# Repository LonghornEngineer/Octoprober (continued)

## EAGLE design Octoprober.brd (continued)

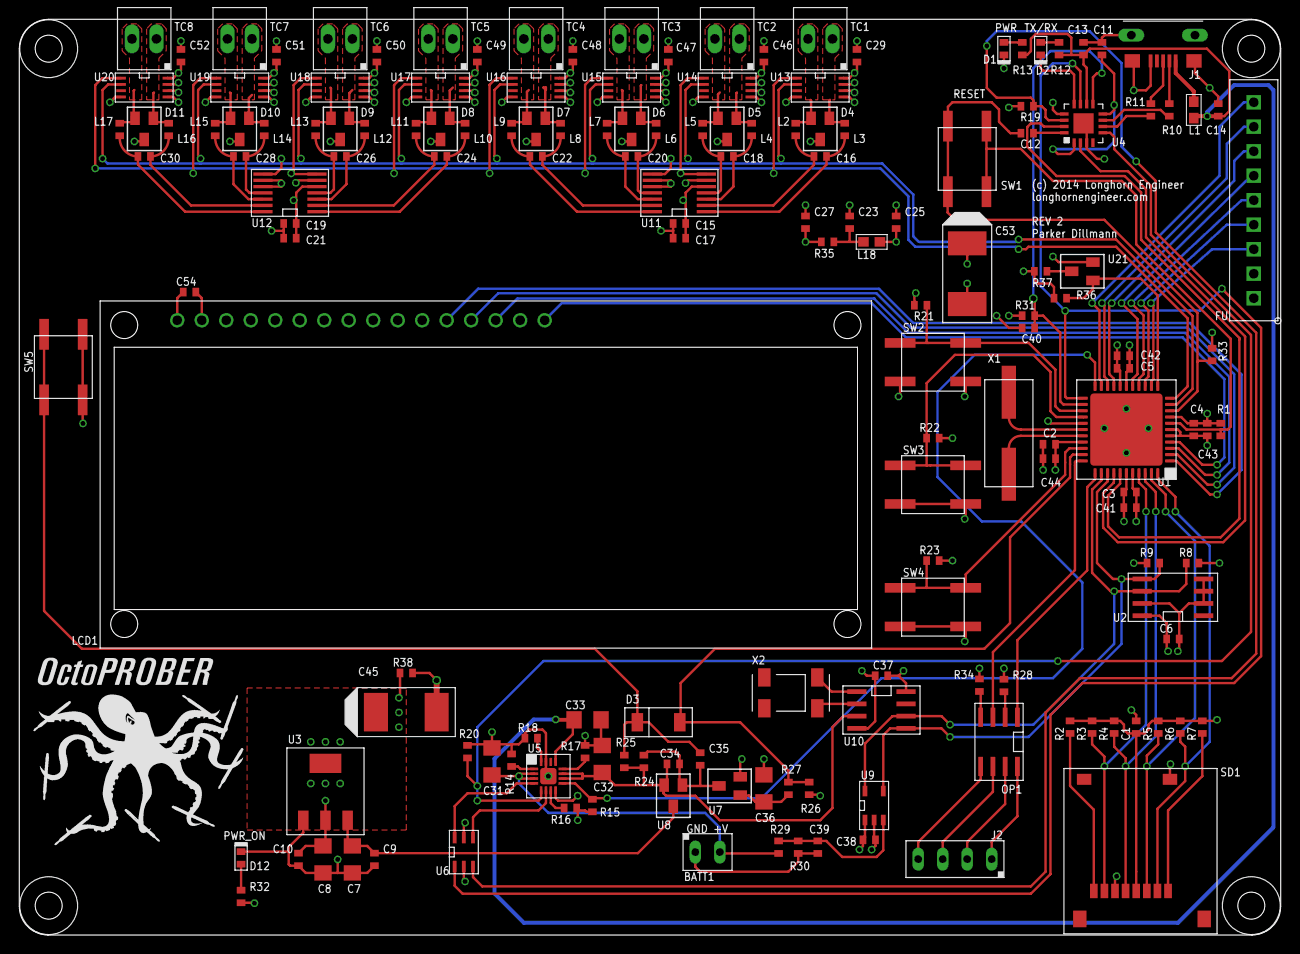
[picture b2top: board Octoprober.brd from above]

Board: 4 copper layers, 130.8 x 95.0 mm, 171 parts (0 on the bottom side), 109 nets.

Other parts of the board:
U$3, U$4, U$5, U$6: MOUNT_HOLE_2.8MM

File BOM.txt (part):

Partlist exported from C:/Users/ParkerD/Documents/GitHub/Octoprober/Octoprober.sch at 2/24/2014 9:25:52 PM

Qty Value                 Device                        Package                       Parts                                                                                                                     Description                    
1                         HD44780_LCD1602_COUNTERSINK   CHAR_DISPLAY_1602_COUNTERSINK LCD1                                                                                                                                                     
1                         PH_1X04HEADER_PTH             HEADER_01X04_PTH              J2                                                                                                                        4 Pin Connectors               
8   0.01uF                CAPACITOR_NON_POLAR0402       0402                          C16, C18, C20, C22, C24, C26, C28, C30                                                                                    Capacitor Non Polarized        
26  0.1uF                 CAPACITOR_NON_POLAR0402       0402                          C1, C2, C3, C4, C5, C6, C9, C10, C11, C12, C13, C14, C15, C17, C19, C21, C23, C25, C27, C29, C34, C35, C37, C38, C39, C40 Capacitor Non Polarized        
1   1.13K                 RESISTOR0402                  0402                          R18                                                                                                                       Resistors                      
1   1.18K                 RESISTOR0402                  0402                          R17                                                                                                                       Resistors                      
3   100K                  RESISTOR0402                  0402                          R24, R26, R29                                                                                                             Resistors                      
1   10118193-0001LF       USB10118193-0001LF            10118193-0001LF               J1                                                                                                                                                       
20  10K                   RESISTOR0402                  0402                          R1, R2, R3, R4, R5, R6, R7, R8, R9, R14, R15, R16, R19, R20, R21, R22, R23, R25, R31, R33                                 Resistors                      
6   10uF                  CAPACITOR_NON_POLAR1206       1206                          C7, C8, C31, C32, C33, C36                                                                                                Capacitor Non Polarized        
2   120                   RESISTOR0402                  0402                          R28, R34                                                                                                                  Resistors                      
2   22                    RESISTOR0402                  0402                          R10, R11                                                                                                                  Resistors                      
1   254K                  RESISTOR0402                  0402                          R30                                                                                                                       Resistors                      
8   282834-2              PH_1X02SCREW_TERM             HEADER_01X02_PTH_SCREWTERM    TC1, TC2, TC3, TC4, TC5, TC6, TC7, TC8                                                                                    2 pin connectors               
1   300K                  RESISTOR0402                  0402                          R27                                                                                                                       Resistors                      
3   330                   RESISTOR0402                  0402                          R12, R13, R32                                                                                                             Resistors                      
1   502570-0893           SD_CARD502570-0893            502570-0893                   SD1                                                                                                                                                      
3   598-8070-107F         LED_SINGLE0402                LED_0402                      D1, D2, D12                                                                                                                                              
1   74HC2G04GV,125        74HCT2G04GV,125TTSOP-6        TTSOP-6                       U6                                                                                                                                                       
1   ABLS3-6.000MHZ-D4Y-T  CRYSTALHC-49                  HC-49/US_SM                   X1                                                                                                                                                       
1   ABS25-32.768KHz-1-T   CRYSTAL8MM_X_3.8MM            8MM_X_3.8MM                   X2                                                                                                                                                       
1   ACPL-227              ACPL-227SOIC-8                SOIC-8                        OP1                                                                                                                                                      
1   ADP3338AKCZ-3.3-RL    FIXED_VOLTAGE_REGSOT-223_ALT  SOT-223                       U3                                                                                                                                                       
16  BK1005HM471-T         INDUCTOR0402                  0402                          L2, L3, L4, L5, L6, L7, L8, L9, L10, L11, L12, L13, L14, L15, L16, L17                                                    Inductors                      
1   BQ24075RGTT           BQ2407XQFN-16                 QFN-16_BOT_PAD                U5                                                                                                                                                       
1   CAT24C512WI-GT3       CAT24M01XI-T2SOIC-8_W         SOIC-8_W                      U2                                                                                                                                                       
1   DS1340Z-33+           DS1340SOIC-8                  SOIC-8                        U18                                                                                                                                                      
5   EVQ-Q2203W            SPSTEVQ-Q2203W                EVQ-Q2203W                    SW1, SW2, SW3, SW4, SW5                                                                                                   SPST Switches                  
1   FT230XQ-R             FT230XQFN-16                  QFN-16                        U4                                                                                                                        Manufacturer Part #: FT230XS-R 
1   LHE_FRAME             LHE_FRAME                     LHE_FRAME                     U$1                                                                                                                                                      
8   MAX31855KASA+         MAX31855SO-8                  SO-8                          U7, U8, U9, U10, U11, U12, U13, U14                                                                                                                      
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
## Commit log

2013-12-16 Commit first schematic. Need to figure out power.
2013-12-16 Added lithium battery. Still need to add charger.
2013-12-17 Added BQ24075RGTT for charging.
2013-12-18 Still need Battery Monitoring Solution
2013-12-18 Uploading PDF of Logo
2013-12-19 Added Soft power switch
    Soft power circuit to enable MCU to initiate a shutdown of the system to
    prevent corruption of the SD Card.
2013-12-19 Added ADC. Might use it for battery voltage level.
2013-12-31 Created Board. Still need to figure out connector
2014-01-06 Worked on the layout some more.
    Still need lots of work and connectors.
2014-01-07 Add optocouple.
2014-01-07 Finished preliminary routing
2014-01-07 Added Schematic image.
2014-01-10 Added RTC.
2014-01-10 New Schematic image
2014-01-10 Rerouted I/O for LCD around mounting hole
2014-01-11 Working on Silkscreen
2014-01-12 Fixed some traces. Looking good. Silkscreen next.
2014-01-13 Added TVS to TC lines.
2014-01-13 Finished REV0.
2014-01-14 Added ADC MCP3021 to monitor battery
2014-01-14 Cam files REV0
2014-01-27 Push Schematic image
2014-01-27 removed camfiles
2014-01-27 removed old layout images.
2014-01-28 Added part values and created BOM.txt
2014-01-28 Fixed some part numbers
2014-01-28 Finished BOM...I hope.
2014-01-31 Swapped VCC and VDD on display
2014-01-31 Updated display footprint
2014-01-31 Evened out power traces on C17
2014-02-04 Changed footprint for Regulator
2014-02-04 Changed FT230X RST to be controlled by PROP
2014-02-04 Added cap to FT230X RST line.
2014-02-04 Fixed screw terminal footprints.
2014-02-05 Added Code section for OctoPROBER
2014-02-05 Added README.md to code
2014-02-05 Cleaned up LCD Driver
2014-02-05 Added Serial LCD Code. Not Tested.
2014-02-06 LCD Screen is Serial now.
    Wrote spin code for Serial interface.
2014-02-06 Added code for Reset function.
2014-02-06 changed how the RESET condition worked for test.
2014-02-06 Updated images and fixed format issue in code
2014-02-06 I changed something?
2014-02-07 Changed what to reset on.
2014-02-08 Added code to get ADC MCP3021 working
2014-02-09 Added test code for RTC
2014-02-10 Added driver for the MAX31855. Needs rewrite.
2014-02-11 REV1 finished routing. Need to increase font size.
2014-02-11 Changed line weights. Need to test SD card slot.
2014-02-12 Fixed SD card. Need GND pin routed.
2014-02-12 Updating Layout and Schematic images.
2014-02-18 Moving code to Octocoder repository
2014-02-24 Updated LCD display to be wider. Fixed a Via dia.
2014-02-25 Updated BOM to current
2014-02-25 Updated Crystal part number
2014-02-25 Fixed layout of display
2014-03-04 Added template for FT230X
2014-03-05 Added more decoupling around the Propeller
2014-03-06 Removed MAX31855. Added MCP3424 instead!
2014-03-07 Finished the new MCP3424 and AT30TSE752-XM8-T
2014-03-14 Added another 470uF cap
2014-03-16 Fixed the template file.
2014-03-17 Added 560ohm resistor to discharge caps.
2014-03-18 Fixed FT230X to support BC1.2 chargers.
2014-03-19 REV 2 push
2014-03-19 Latest BOM.txt
2015-01-12 Merged with Octocoder.
2015-10-22 New chips for thermocouples.
2015-10-23 Working on LCD setup. Need to find a case.
2015-10-23 Thermocouple connectors added.
2015-11-02 Switched display to a ERC128128FS
2016-06-24 starting on the revamp.
2016-06-27 Working on new rev. Need to route.
2016-06-28 Started routing REV3.
2016-07-12 More work to check in.
